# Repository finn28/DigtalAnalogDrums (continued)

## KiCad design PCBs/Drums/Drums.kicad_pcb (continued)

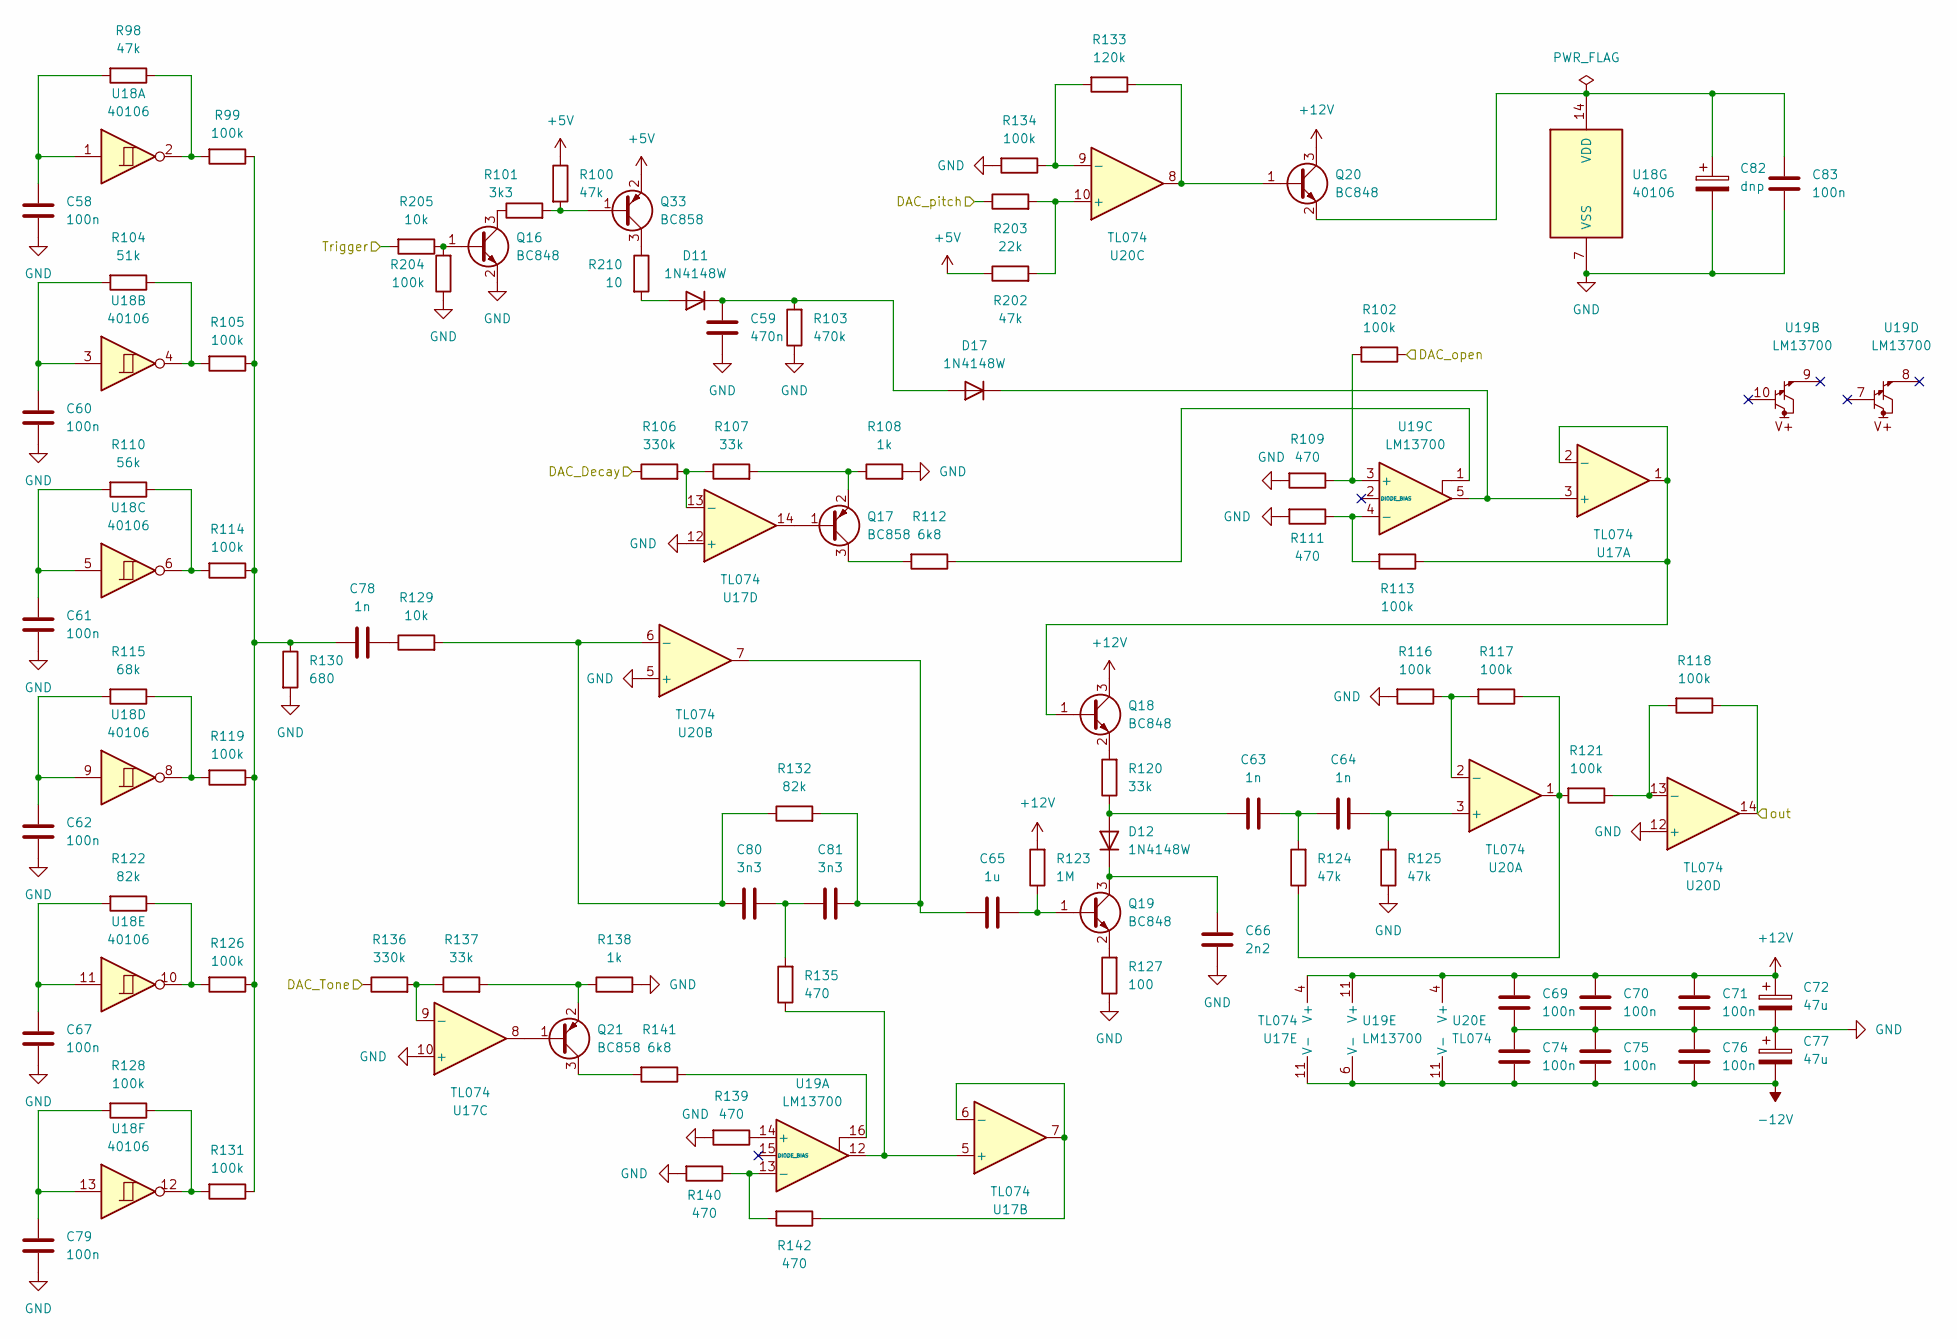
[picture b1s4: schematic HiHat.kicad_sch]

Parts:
C58, C60, C61, C62, C67, C79: 100n; C_Disc_D7.0mm_W2.5mm_P5.00mm
C59: 470n; C_Rect_L7.2mm_W3.5mm_P5.00mm_FKS2_FKP2_MKS2_MKP2
C63, C64, C78: 1n; C_Disc_D7.0mm_W2.5mm_P5.00mm
C65: 1u; C_Rect_L7.2mm_W5.0mm_P5.00mm
C66: 2n2; C_Disc_D7.0mm_W2.5mm_P5.00mm
C69, C70, C71, C74, C75, C76, C83: 100n; C_0402_1005Metric_Pad0.74x0.62mm_HandSolder
C72, C77: 47u; CP_Elec_5x5.9
C80, C81: 3n3; C_Disc_D7.0mm_W2.5mm_P5.00mm
C82: dnp; CP_Elec_5x5.9
D11, D12, D17: 1N4148W; D_SOD-123
Q16, Q18, Q19, Q20: BC848; SOT-23
Q17, Q21, Q33: BC858; SOT-23
R98, R100, R124, R125, R202: 47k; R_0805_2012Metric_Pad1.20x1.40mm_HandSolder
R99, R102, R105, R113, R114, R116, R117, R118, R119, R121, R126, R128, R131, R134, R204: 100k; R_0805_2012Metric_Pad1.20x1.40mm_HandSolder
R101: 3k3; R_0805_2012Metric_Pad1.20x1.40mm_HandSolder
R103: 470k; R_0805_2012Metric_Pad1.20x1.40mm_HandSolder
R104: 51k; R_0805_2012Metric_Pad1.20x1.40mm_HandSolder
R106, R136: 330k; R_0805_2012Metric_Pad1.20x1.40mm_HandSolder
R107, R120, R137: 33k; R_0805_2012Metric_Pad1.20x1.40mm_HandSolder
R108, R138: 1k; R_0805_2012Metric_Pad1.20x1.40mm_HandSolder
R109, R111, R135, R139, R140, R142: 470; R_0805_2012Metric_Pad1.20x1.40mm_HandSolder
R110: 56k; R_0805_2012Metric_Pad1.20x1.40mm_HandSolder
R112, R141: 6k8; R_0805_2012Metric_Pad1.20x1.40mm_HandSolder
R115: 68k; R_0805_2012Metric_Pad1.20x1.40mm_HandSolder
R122, R132: 82k; R_0805_2012Metric_Pad1.20x1.40mm_HandSolder
R123: 1M; R_0805_2012Metric_Pad1.20x1.40mm_HandSolder
R127: 100; R_0805_2012Metric_Pad1.20x1.40mm_HandSolder
R129, R205: 10k; R_0805_2012Metric_Pad1.20x1.40mm_HandSolder
R130: 680; R_0805_2012Metric_Pad1.20x1.40mm_HandSolder
R133: 120k; R_0805_2012Metric_Pad1.20x1.40mm_HandSolder
R203: 22k; R_0805_2012Metric_Pad1.20x1.40mm_HandSolder
R210: 10; R_0805_2012Metric_Pad1.20x1.40mm_HandSolder
U17, U20: TL074; TSSOP-14_4.4x5mm_P0.65mm
U18: 40106; SOIC-14_3.9x8.7mm_P1.27mm
U19: LM13700; SOIC-16_3.9x9.9mm_P1.27mm

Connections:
+5V: Q33.2 (E), R100.1, R202.1; also elsewhere on the board
+12V: C69.1, C70.1, C71.1, C72.1, Q18.3 (C), Q20.3 (C), R123.2, U17.4 (V+), U19.11 (V+), U20.4 (V+); also elsewhere on the board
-12V: C74.2, C75.2, C76.2, C77.2, U17.11 (V-), U19.6 (V-), U20.11 (V-); also elsewhere on the board
/HiHat/out: R118.1, U20.14; also elsewhere on the board
/HiHat_Trig: R205.2; also elsewhere on the board
/dac9: R136.1; also elsewhere on the board
/dac10: R106.1; also elsewhere on the board
/dac11: R102.1; also elsewhere on the board
/dac12: R203.1; also elsewhere on the board
GND: C58.2, C59.1, C60.2, C61.2, C62.2, C66.1, C67.2, C69.2, C70.2, C71.2, C72.2, C74.1, C75.1, C76.1, C77.1, C79.2, C82.2, C83.2, Q16.2 (E), R103.1, R108.2, R109.2, R111.2, R116.2, R125.1, R127.1, R130.2, R134.2, R138.2, R139.2, R140.2, R204.1, U17.10 (+), U17.12 (+), U18.7 (VSS), U20.5 (+), U20.12 (+); also elsewhere on the board
unnamed: C58.1, R98.2, U18.1
unnamed: C60.1, R104.2, U18.3
unnamed: C61.1, R110.2, U18.5
unnamed: C62.1, R115.2, U18.9
unnamed: C63.2, C64.1, R124.2
unnamed: C65.1, C81.2, R132.2, U20.7
unnamed: C67.1, R122.2, U18.11
unnamed: C78.1, R99.1, R105.1, R114.1, R119.1, R126.1, R130.1, R131.1
unnamed: C78.2, R129.1
unnamed: C79.1, R128.2, U18.13
unnamed: C80.2, C81.1, R135.2
unnamed: D11.2 (A), R210.2
unnamed: C59.2, D11.1 (K), D17.2 (A), R103.2
unnamed: C63.1, D12.2 (A), R120.1
unnamed: C66.2, D12.1 (K), Q19.3 (C)
unnamed: D17.1 (K), U17.3 (+), U19.5
unnamed: Q16.1 (B), R204.2, R205.1
unnamed: Q16.3 (C), R101.1
unnamed: Q17.1 (B), U17.14
unnamed: Q17.3 (C), R112.2
unnamed: Q17.2 (E), R107.2, R108.1
unnamed: Q18.1 (B), R113.1, U17.1, U17.2 (-)
unnamed: Q18.2 (E), R120.2
unnamed: C65.2, Q19.1 (B), R123.1
unnamed: Q19.2 (E), R127.2
unnamed: Q20.1 (B), R133.1, U20.8
unnamed: C82.1, C83.1, Q20.2 (E), U18.14 (VDD)
unnamed: Q21.1 (B), U17.8
unnamed: Q21.3 (C), R141.2
unnamed: Q21.2 (E), R137.2, R138.1
unnamed: Q33.1 (B), R100.2, R101.2
unnamed: Q33.3 (C), R210.1
unnamed: R98.1, R99.2, U18.2
unnamed: R104.1, R105.2, U18.4
unnamed: R110.1, R114.2, U18.6
unnamed: R112.1, U19.1
unnamed: R115.1, R119.2, U18.8
unnamed: R117.1, R121.2, R124.1, U20.1
unnamed: R122.1, R126.2, U18.10
unnamed: R128.1, R131.2, U18.12
unnamed: R141.1, U19.16
unnamed: R135.1, U17.5 (+), U19.12
unnamed: R142.1, U17.6 (-), U17.7
unnamed: R136.2, R137.1, U17.9 (-)
unnamed: R106.2, R107.1, U17.13 (-)
unnamed: R139.1, U19.14 (+)
unnamed: R140.1, R142.2, U19.13 (-)
unnamed: R102.2, R109.1, U19.3 (+)
unnamed: R111.1, R113.2, U19.4 (-)
unnamed: C64.2, R125.2, U20.3 (+)
unnamed: R116.1, R117.2, U20.2 (-)
unnamed: C80.1, R129.2, R132.1, U20.6 (-)
unnamed: R202.2, R203.2, U20.10 (+)
unnamed: R133.2, R134.1, U20.9 (-)
unnamed: R118.2, R121.1, U20.13 (-)

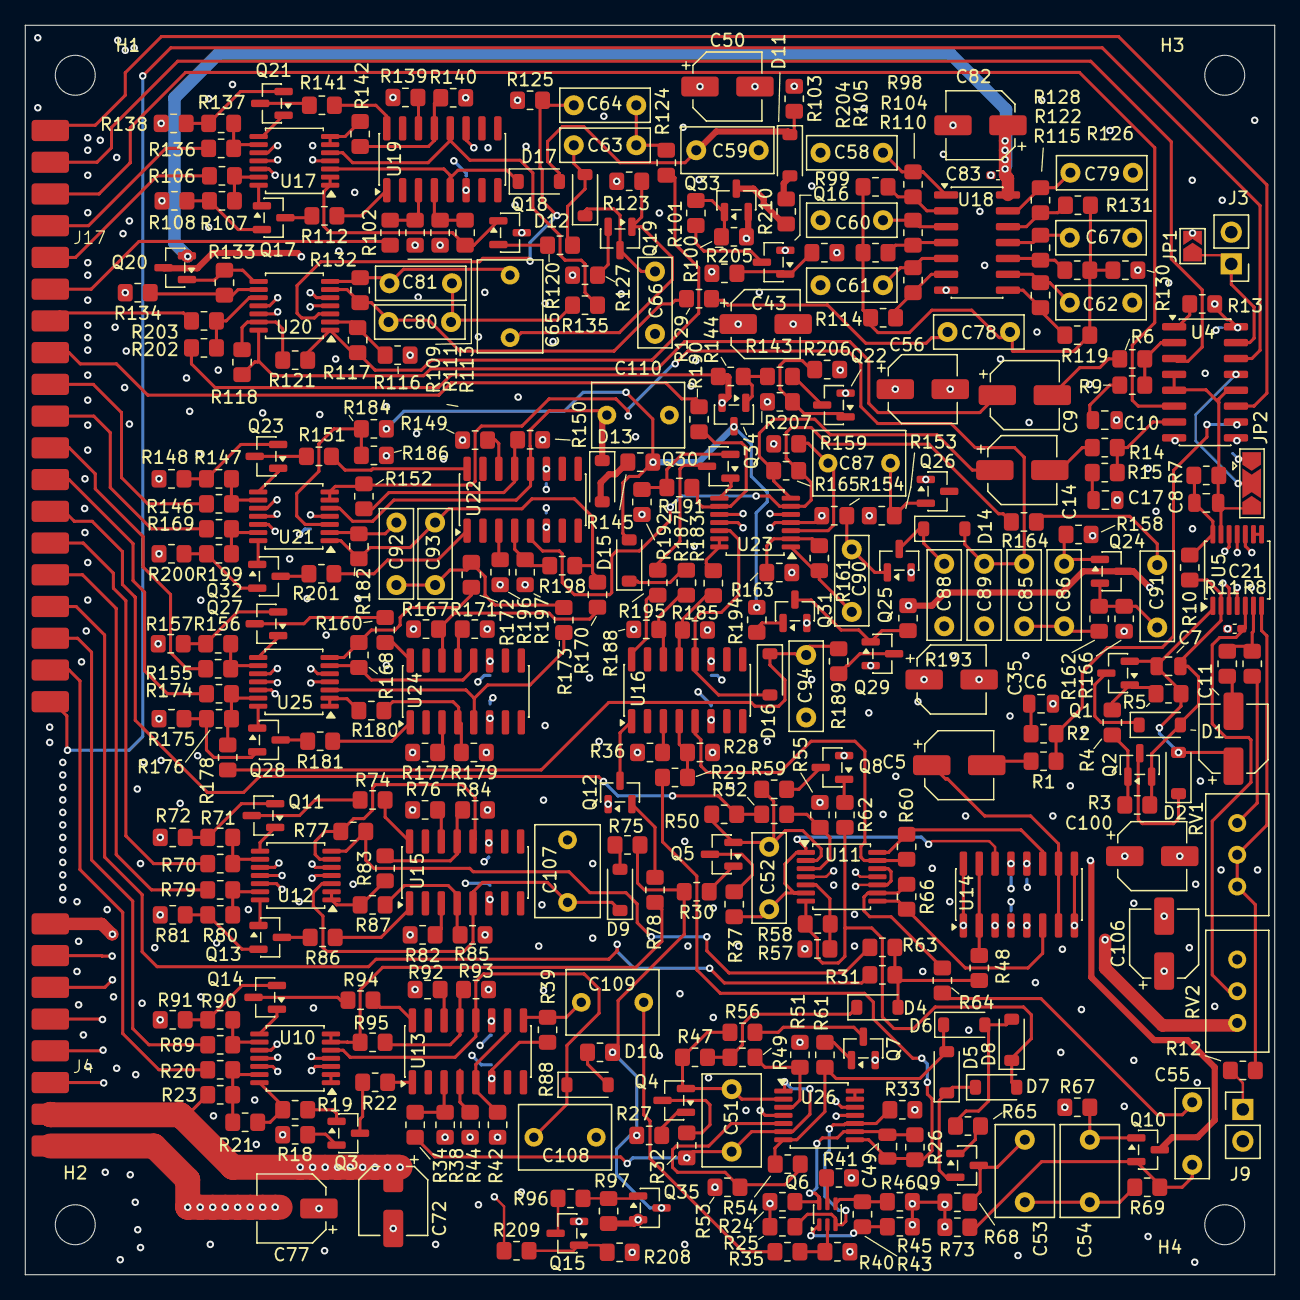
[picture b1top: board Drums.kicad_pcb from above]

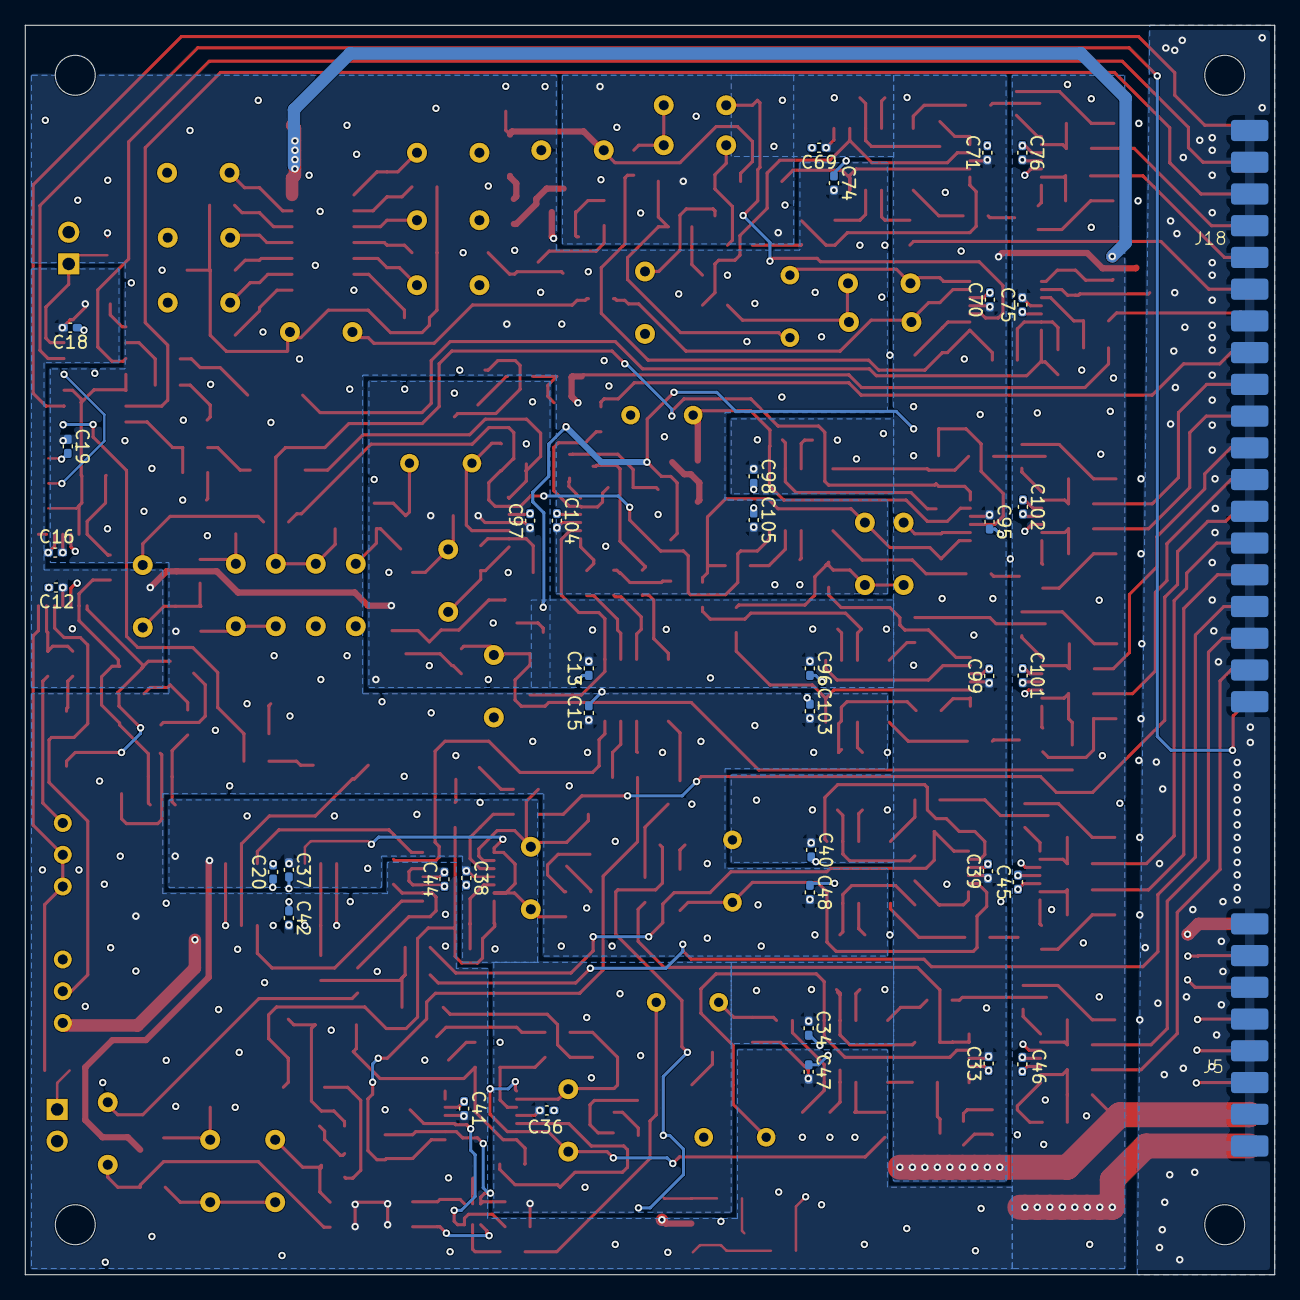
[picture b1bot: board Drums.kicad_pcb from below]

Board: 4 copper layers, 100.0 x 100.0 mm, 383 parts (39 on the bottom side), 271 nets.

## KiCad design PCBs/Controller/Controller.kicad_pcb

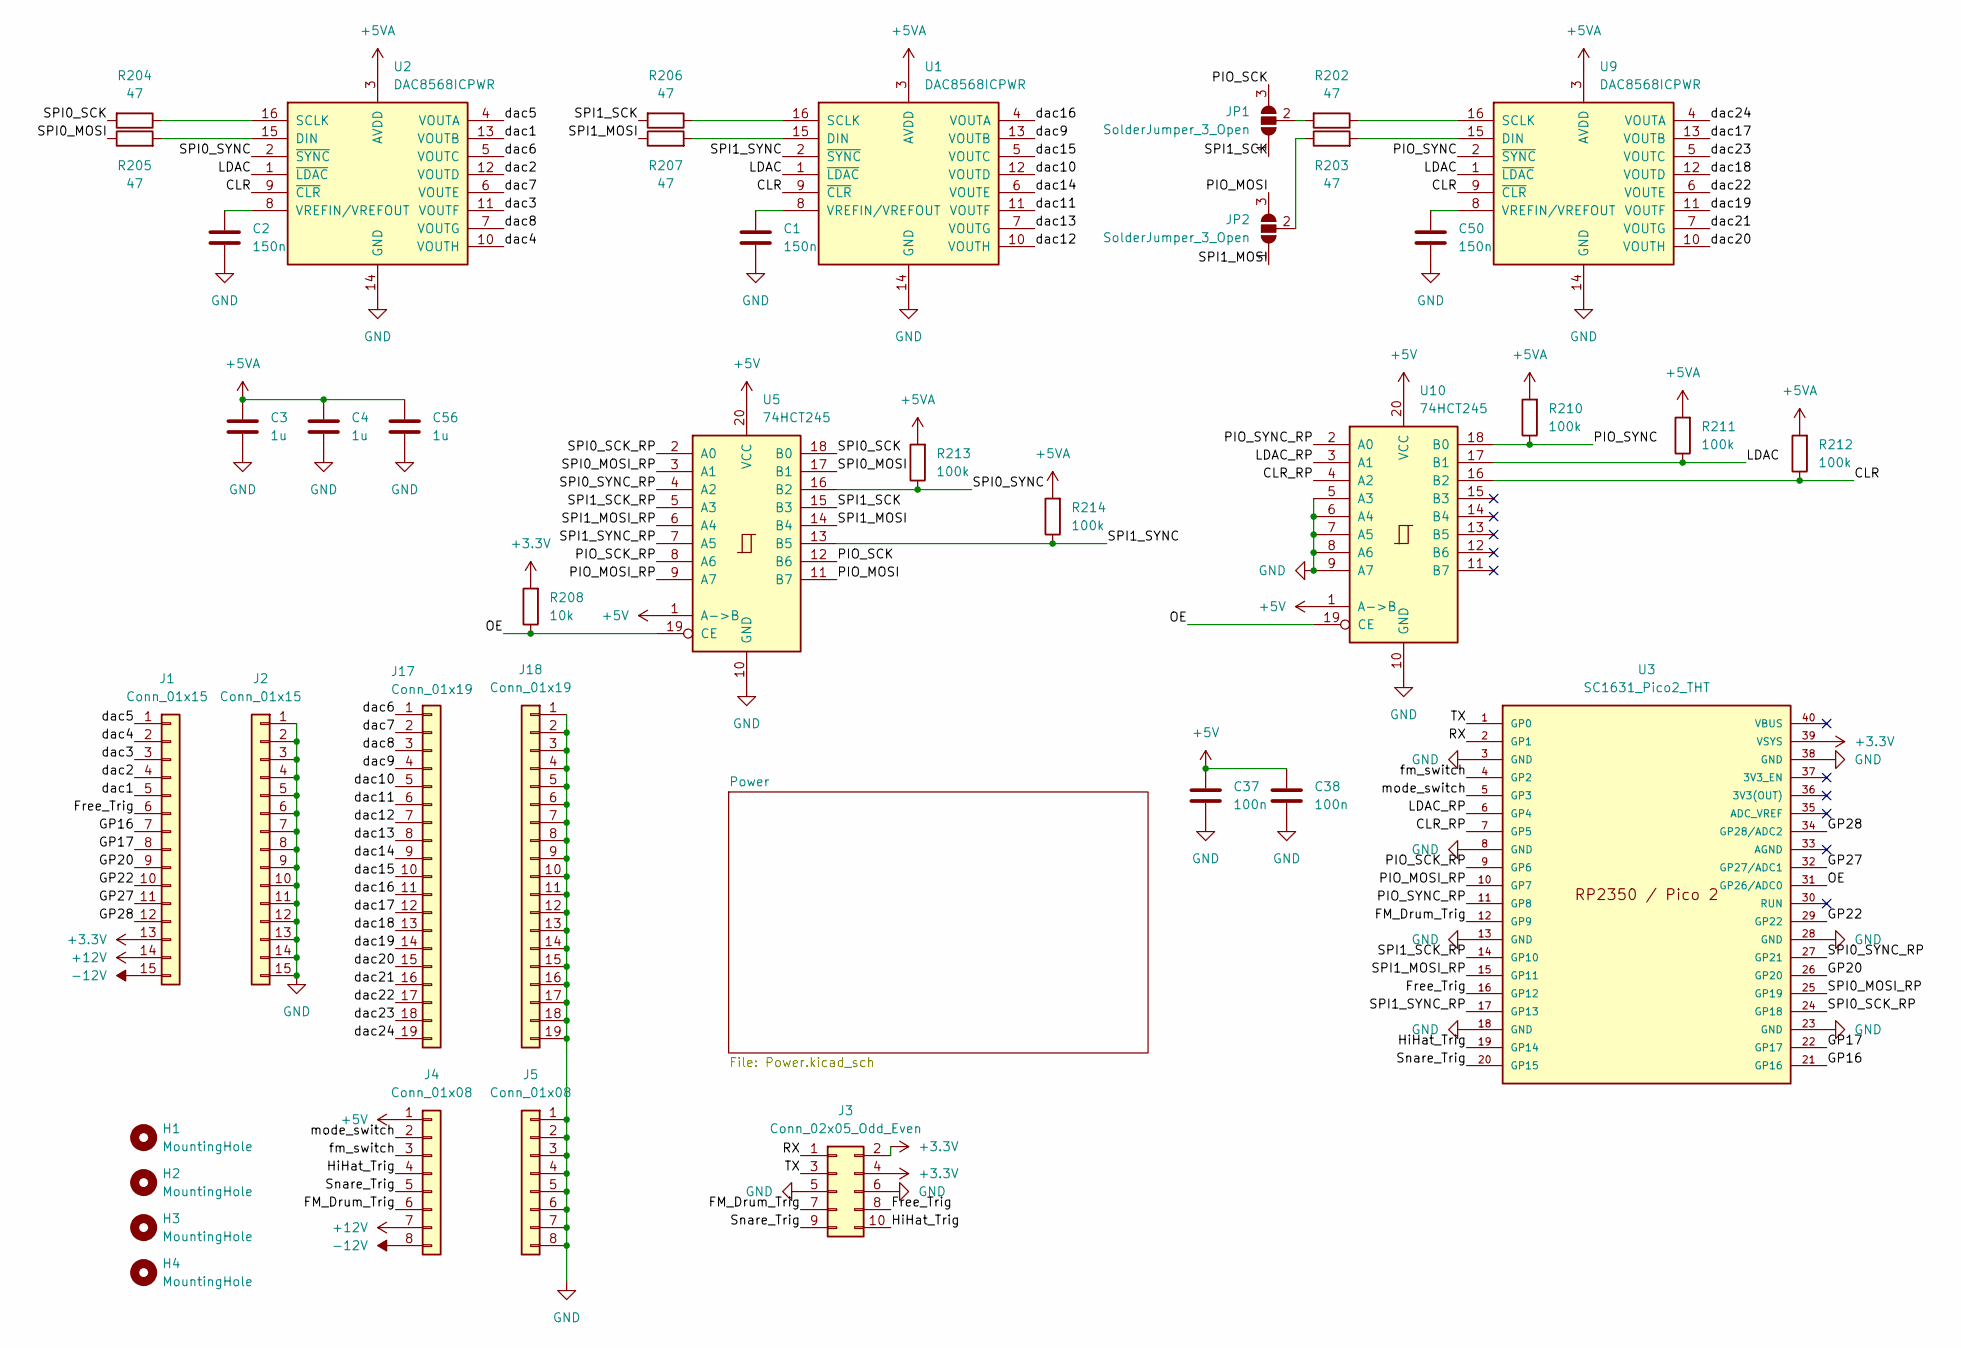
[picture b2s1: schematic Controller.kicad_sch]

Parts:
C1, C2, C50: 150n; C_0805_2012Metric
C3, C4, C56: 1u; C_0805_2012Metric
C37, C38: 100n; C_0402_1005Metric_Pad0.74x0.62mm_HandSolder
H1, H2, H3, H4: MountingHole; MountingHole_3.2mm_M3
J1, J2: Conn_01x15; SMD Con15
J3: Conn_02x05_Odd_Even; IDC-Header_2x05_P2.54mm_Vertical
J4, J5: Conn_01x08; SMD Con8
J17, J18: Conn_01x19; SMD Con19
JP1, JP2: SolderJumper_3_Open; SolderJumper-3_P2.0mm_Open_TrianglePad1.0x1.5mm
R202, R203, R204, R205, R206, R207: 47; R_0805_2012Metric_Pad1.20x1.40mm_HandSolder
R208: 10k; R_0805_2012Metric_Pad1.20x1.40mm_HandSolder
R210, R211, R212, R213, R214: 100k; R_0805_2012Metric_Pad1.20x1.40mm_HandSolder
U1, U2, U9: DAC8568ICPWR; TSSOP-16_4.4x5mm_P0.65mm; Mouser 595-DAC8568ICPWR
U3: SC1631_Pico2_THT; Pico2_SC1631_SMD_HandSolder; Mouser 358-SC1631
U5, U10: 74HCT245; SO-20_5.3x12.6mm_P1.27mm

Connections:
+3.3V: J1.13, J3.2, J3.4, R208.2, U3.39 (VSYS); also elsewhere on the board
+5V: C37.1, C38.1, J4.1, U5.1 (A->B), U5.20 (VCC), U10.1 (A->B), U10.20 (VCC); also elsewhere on the board
+5VA: C3.2, C4.2, C56.2, R210.2, R211.2, R212.2, R213.2, R214.2, U1.3 (AVDD), U2.3 (AVDD), U9.3 (AVDD); also elsewhere on the board
+12V: J1.14, J4.7; also elsewhere on the board
-12V: J1.15, J4.8; also elsewhere on the board
/CLR: R212.1, U1.9 (~CLR), U2.9 (~CLR), U9.9 (~CLR), U10.16 (B2)
/CLR_RP: U3.7 (GP5), U10.4 (A2)
/FM_Drum_Trig: J3.7, J4.6, U3.12 (GP9)
/Free_Trig: J1.6, J3.8, U3.16 (GP12)
/GP16: J1.7, U3.21 (GP16)
/GP17: J1.8, U3.22 (GP17)
/GP20: J1.9, U3.26 (GP20)
/GP22: J1.10, U3.29 (GP22)
/GP27: J1.11, U3.32 (GP27/ADC1)
/GP28: J1.12, U3.34 (GP28/ADC2)
/HiHat_Trig: J3.10, J4.4, U3.19 (GP14)
/LDAC: R211.1, U1.1 (~LDAC), U2.1 (~LDAC), U9.1 (~LDAC), U10.17 (B1)
/LDAC_RP: U3.6 (GP4), U10.3 (A1)
/OE: R208.1, U3.31 (GP26/ADC0), U5.19 (CE), U10.19 (CE)
/PIO_MOSI: JP2.3 (B), U5.11 (B7)
/PIO_MOSI_RP: U3.10 (GP7), U5.9 (A7)
/PIO_SCK: JP1.3 (B), U5.12 (B6)
/PIO_SCK_RP: U3.9 (GP6), U5.8 (A6)
/PIO_SYNC: R210.1, U9.2 (~SYNC), U10.18 (B0)
/PIO_SYNC_RP: U3.11 (GP8), U10.2 (A0)
/RX: J3.1, U3.2 (GP1)
/SPI0_MOSI: R205.1, U5.17 (B1)
/SPI0_MOSI_RP: U3.25 (GP19), U5.3 (A1)
/SPI0_SCK: R204.2, U5.18 (B0)
/SPI0_SCK_RP: U3.24 (GP18), U5.2 (A0)
/SPI0_SYNC: R213.1, U2.2 (~SYNC), U5.16 (B2)
/SPI0_SYNC_RP: U3.27 (GP21), U5.4 (A2)
/SPI1_MOSI: JP2.1 (A), R207.1, U5.14 (B4)
/SPI1_MOSI_RP: U3.15 (GP11), U5.6 (A4)
/SPI1_SCK: JP1.1 (A), R206.2, U5.15 (B3)
/SPI1_SCK_RP: U3.14 (GP10), U5.5 (A3)
/SPI1_SYNC: R214.1, U1.2 (~SYNC), U5.13 (B5)
/SPI1_SYNC_RP: U3.17 (GP13), U5.7 (A5)
/Snare_Trig: J3.9, J4.5, U3.20 (GP15)
/TX: J3.3, U3.1 (GP0)
/dac1: J1.5, U2.13 (VOUTB)
/dac2: J1.4, U2.12 (VOUTD)
/dac3: J1.3, U2.11 (VOUTF)
/dac4: J1.2, U2.10 (VOUTH)
/dac5: J1.1, U2.4 (VOUTA)
/dac6: J17.1, U2.5 (VOUTC)
/dac7: J17.2, U2.6 (VOUTE)
/dac8: J17.3, U2.7 (VOUTG)
/dac9: J17.4, U1.13 (VOUTB)
/dac10: J17.5, U1.12 (VOUTD)
/dac11: J17.6, U1.11 (VOUTF)
/dac12: J17.7, U1.10 (VOUTH)
/dac13: J17.8, U1.7 (VOUTG)
/dac14: J17.9, U1.6 (VOUTE)
/dac15: J17.10, U1.5 (VOUTC)
/dac16: J17.11, U1.4 (VOUTA)
/dac17: J17.12, U9.13 (VOUTB)
/dac18: J17.13, U9.12 (VOUTD)
/dac19: J17.14, U9.11 (VOUTF)
/dac20: J17.15, U9.10 (VOUTH)
/dac21: J17.16, U9.7 (VOUTG)
/dac22: J17.17, U9.6 (VOUTE)
/dac23: J17.18, U9.5 (VOUTC)
/dac24: J17.19, U9.4 (VOUTA)
/fm_switch: J4.3, U3.4 (GP2)
/mode_switch: J4.2, U3.5 (GP3)
GND: C1.1, C2.1, C3.1, C4.1, C37.2, C38.2, C50.1, C56.1, J2.1, J2.2, J2.3, J2.4, J2.5, J2.6, J2.7, J2.8, J2.9, J2.10, J2.11, J2.12, J2.13, J2.14, J2.15, J3.5, J3.6, J5.1, J5.2, J5.3, J5.4, J5.5, J5.6, J5.7, J5.8, J18.1, J18.2, J18.3, J18.4, J18.5, J18.6, J18.7, J18.8, J18.9, J18.10, J18.11, J18.12, J18.13, J18.14, J18.15, J18.16, J18.17, J18.18, J18.19, U1.14 (GND), U2.14 (GND), U3.3 (GND), U3.8 (GND), U3.13 (GND), U3.18 (GND), U3.23 (GND), U3.28 (GND), U3.38 (GND), U5.10 (GND), U9.14 (GND), U10.5 (A3), U10.6 (A4), U10.7 (A5), U10.8 (A6), U10.9 (A7), U10.10 (GND); also elsewhere on the board
unnamed: JP1.2 (C), R202.2
unnamed: JP2.2 (C), R203.1
unnamed: R207.2, U1.15 (DIN)
unnamed: R206.1, U1.16 (SCLK)
unnamed: C1.2, U1.8 (VREFIN/VREFOUT)
unnamed: R205.2, U2.15 (DIN)
unnamed: R204.1, U2.16 (SCLK)
unnamed: C2.2, U2.8 (VREFIN/VREFOUT)
unnamed: R203.2, U9.15 (DIN)
unnamed: R202.1, U9.16 (SCLK)
unnamed: C50.2, U9.8 (VREFIN/VREFOUT)

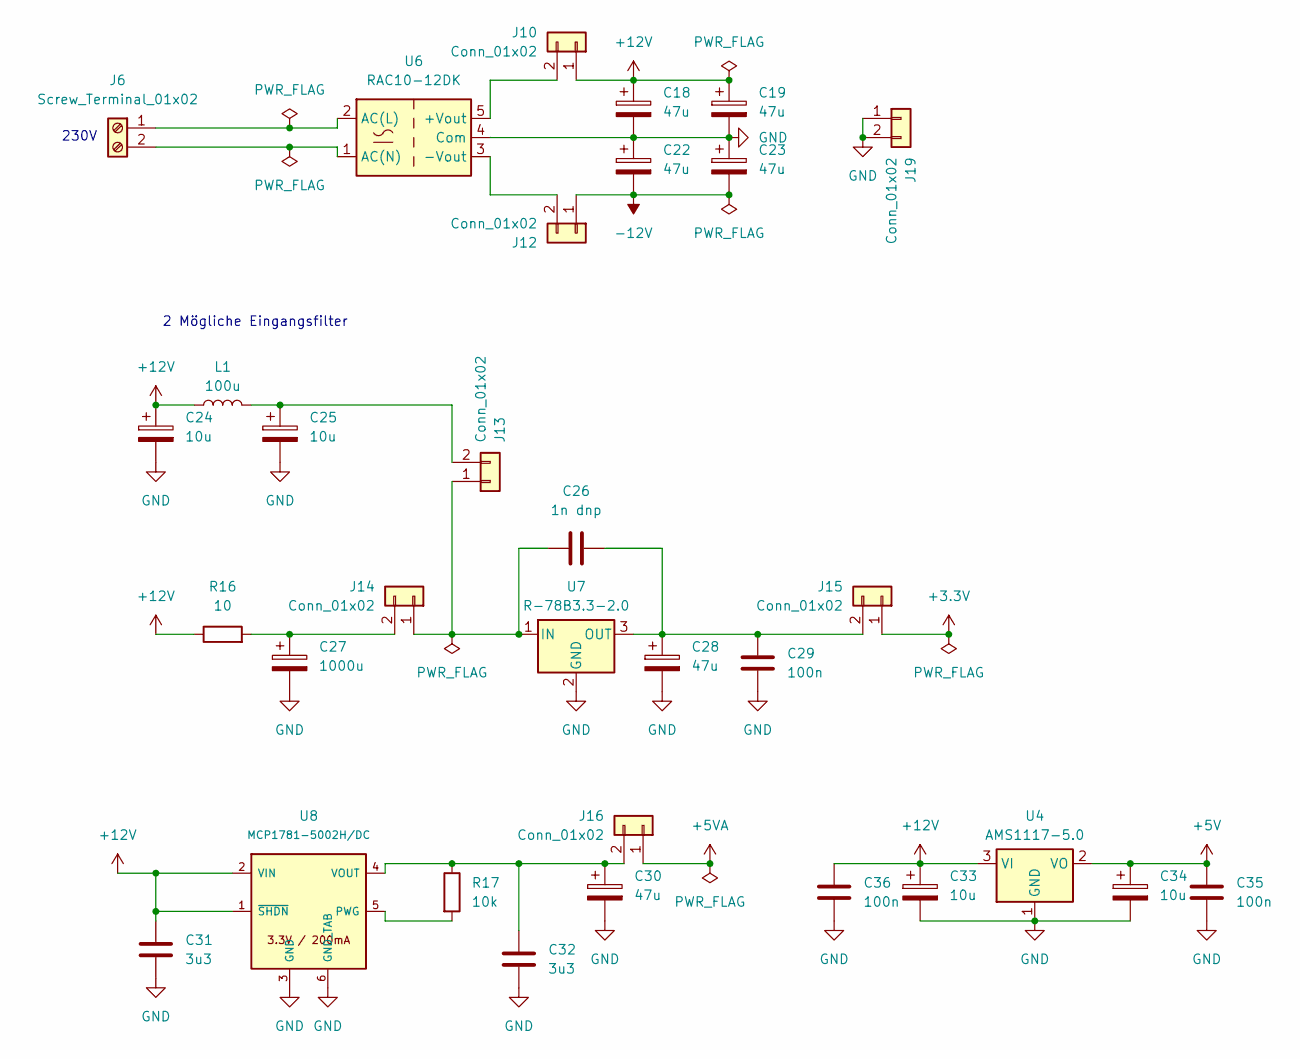
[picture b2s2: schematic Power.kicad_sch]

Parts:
C18, C19, C22, C23, C28, C30: 47u; CP_Elec_5x5.9
C24, C25, C33, C34: 10u; CP_Elec_5x5.9
C26: 1n dnp; C_0805_2012Metric
C27: 1000u; CP_Elec_8x6.9
C29, C35, C36: 100n; C_0402_1005Metric_Pad0.74x0.62mm_HandSolder
C31, C32: 3u3; C_0805_2012Metric
J6: Screw_Terminal_01x02; TerminalBlock_RND_205-00067_1x02_P7.50mm_Horizontal
J10, J12, J13, J14, J15, J16, J19: Conn_01x02; PinHeader_1x02_P2.54mm_Vertical
L1: 100u; L_Wuerth_MAPI-5020
R16: 10; R_2512_6332Metric
R17: 10k; R_0805_2012Metric_Pad1.20x1.40mm_HandSolder
U4: AMS1117-5.0; SOT-223-3_TabPin2
U6: RAC10-12DK; Converter_ACDC_Recom_RAC20-xxDK_THT
U7: R-78B3.3-2.0; Converter_DCDC_RECOM_R-78B-2.0_THT
U8: MCP1781-5002H/DC; MCP1781_SOT-223-5_N7X; Mouser 579-MCP17813302HDC

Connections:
+3.3V: J15.1; also elsewhere on the board
+5V: C34.1, C35.1, U4.2 (VO); also elsewhere on the board
+5VA: J16.1; also elsewhere on the board
+12V: C18.1, C19.1, C24.1, C31.1, C33.1, C36.1, J10.1, L1.1, R16.1, U4.3 (VI), U8.1 (~SHDN), U8.2 (VIN); also elsewhere on the board
-12V: C22.2, C23.2, J12.1; also elsewhere on the board
GND: C18.2, C19.2, C22.1, C23.1, C24.2, C25.2, C27.2, C28.2, C29.2, C30.2, C31.2, C32.2, C33.2, C34.2, C35.2, C36.2, J19.1, J19.2, U4.1 (GND), U6.4 (Com), U7.2 (GND), U8.3 (GND), U8.6 (GND_TAB); also elsewhere on the board
unnamed: J6.1, U6.2 (AC(L))
unnamed: J6.2, U6.1 (AC(N))
unnamed: J10.2, U6.5 (+Vout)
unnamed: J12.2, U6.3 (-Vout)
unnamed: C26.1, J13.1, J14.1, U7.1 (IN)
unnamed: C25.1, J13.2, L1.2
unnamed: C27.1, J14.2, R16.2
unnamed: C26.2, C28.1, C29.1, J15.2, U7.3 (OUT)
unnamed: C30.1, C32.1, J16.2, R17.1, U8.4 (VOUT)
unnamed: R17.2, U8.5 (PWG)

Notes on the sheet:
230V
2 Mögliche Eingangsfilter

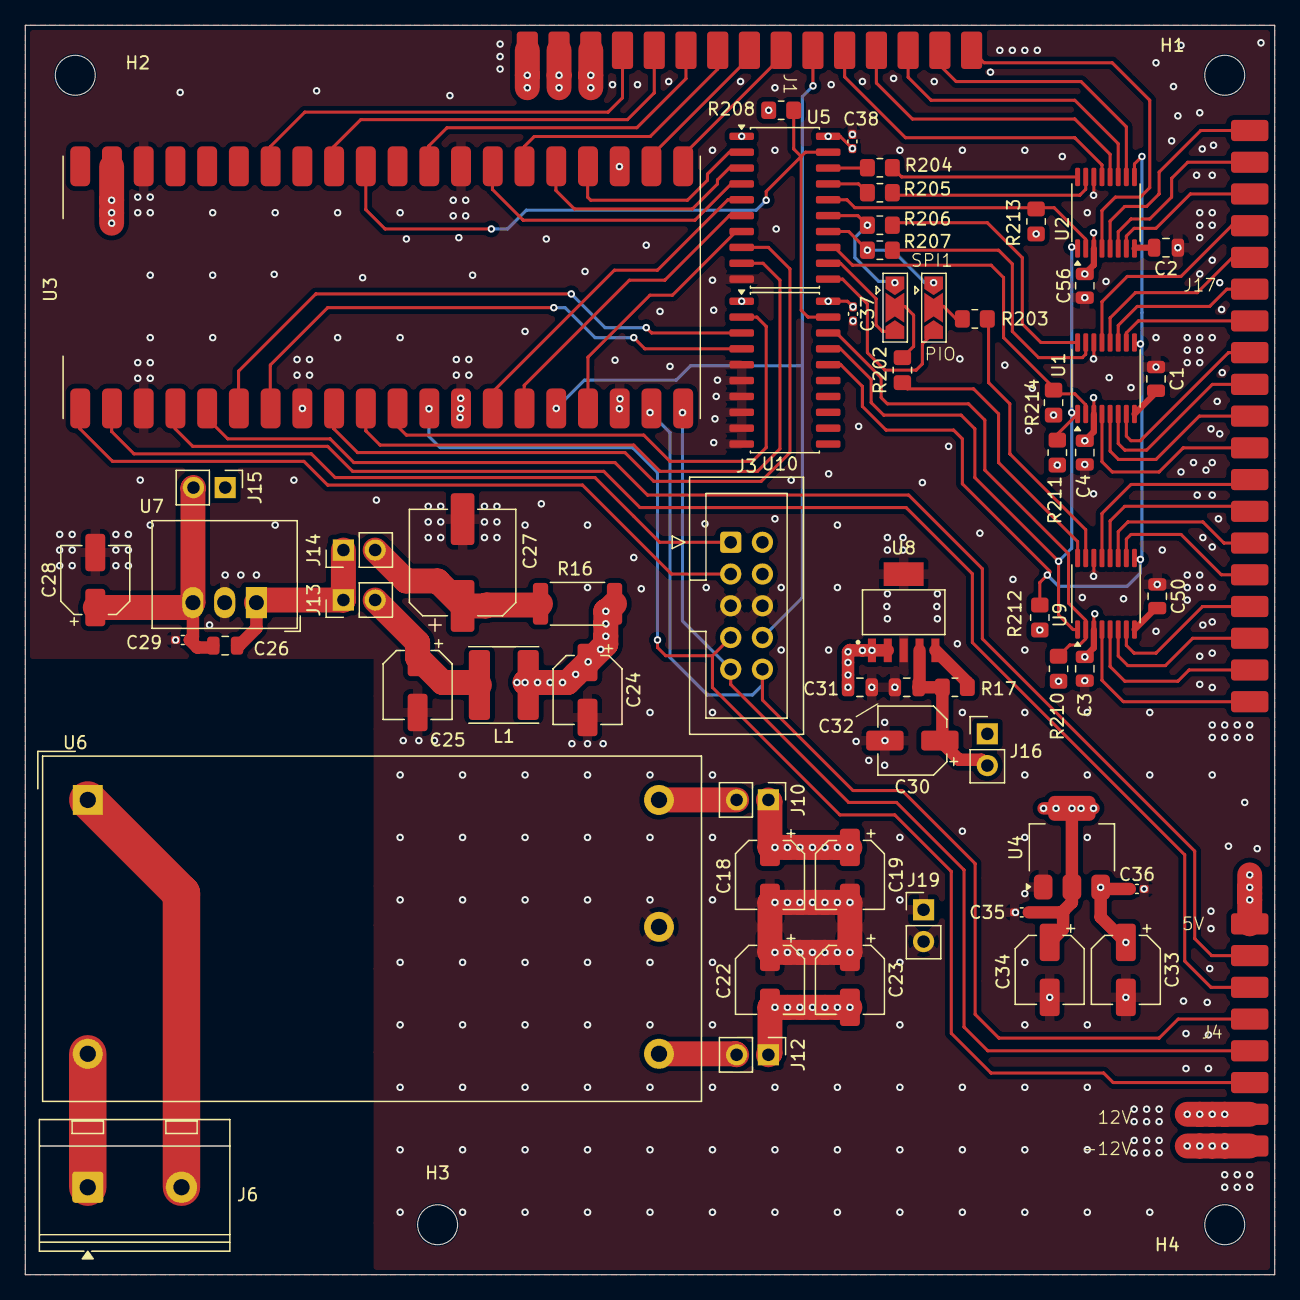
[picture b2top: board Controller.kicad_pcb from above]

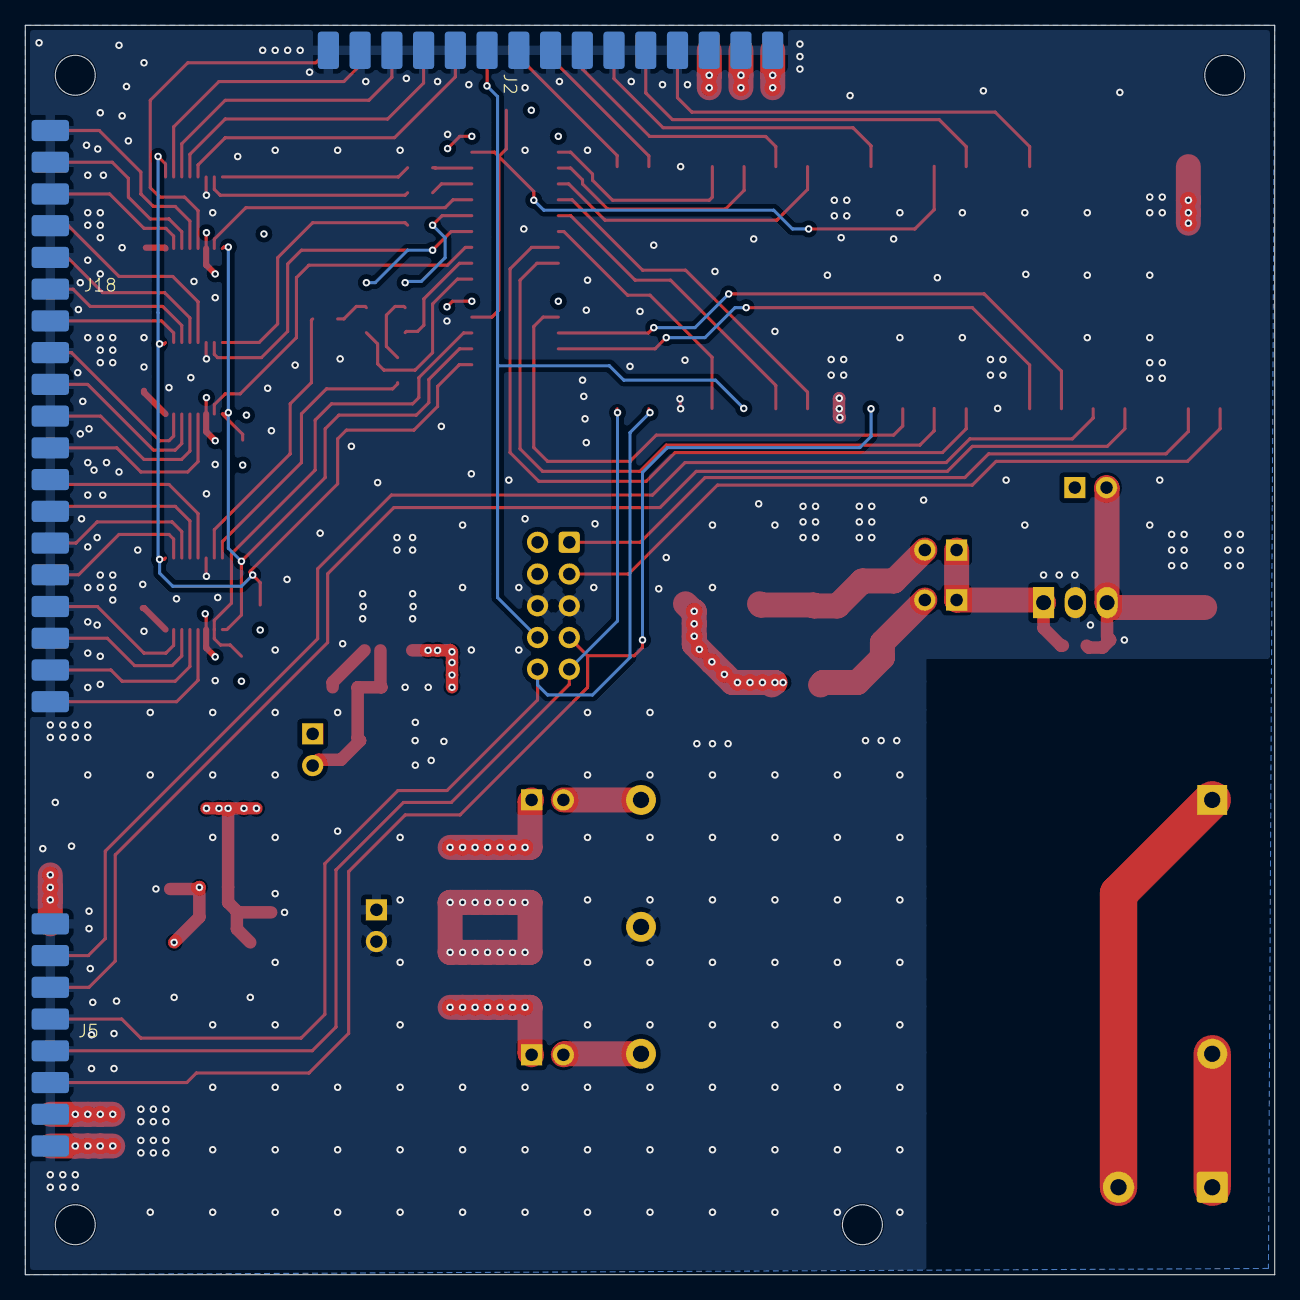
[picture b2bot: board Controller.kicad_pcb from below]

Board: 4 copper layers, 100.0 x 100.0 mm, 71 parts (3 on the bottom side), 88 nets.
